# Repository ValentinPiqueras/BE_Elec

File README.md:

# BE_Elec
Valentin PIQUERAS et Solène DUMAS-GROLLIER
(Groupe E)

Nous avons réalisé le routage, et voici donc notre proposition de routage, cf commit "Proposition Routage Final".

Vous trouverez tous les fichiers corrects dans le dossier PropositionRoutage.

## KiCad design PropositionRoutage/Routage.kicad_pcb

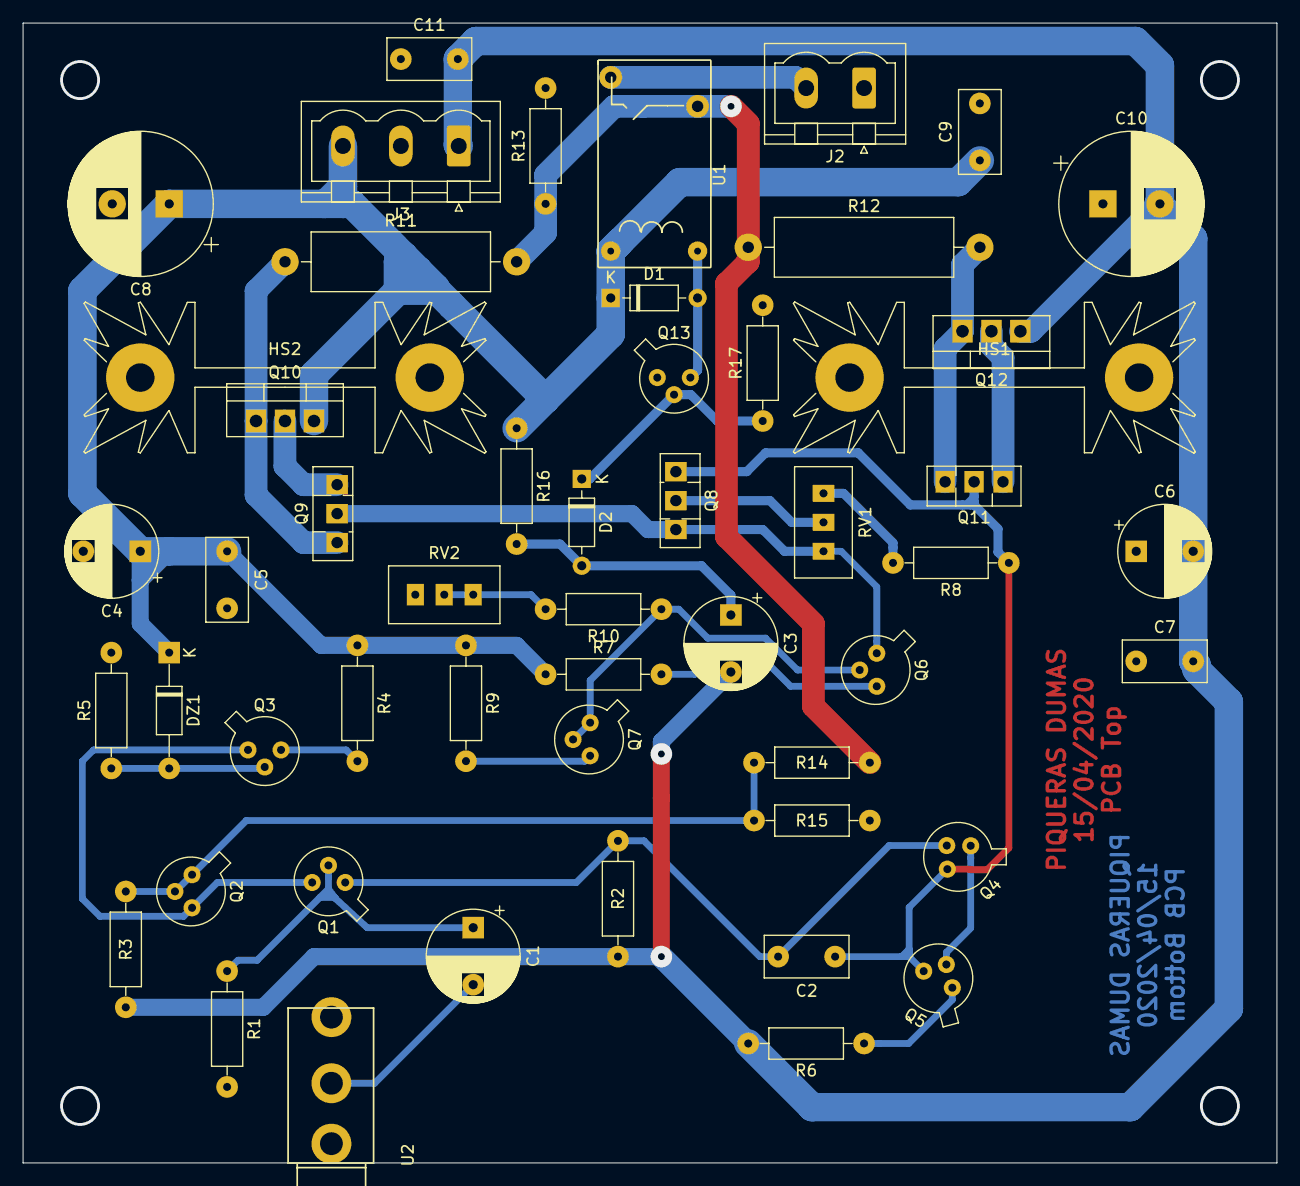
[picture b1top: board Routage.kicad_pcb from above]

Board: 2 copper layers, 110.0 x 100.0 mm, 52 parts (0 on the bottom side), 29 nets.

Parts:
C1, C3: 47u; CP_Radial_D8.0mm_P5.00mm
C2: C; C_Rect_L7.2mm_W3.5mm_P5.00mm_FKS2_FKP2_MKS2_MKP2
C4, C6: 10u; CP_Radial_D8.0mm_P5.00mm
C5, C7, C9, C11: 100n; C_Rect_L7.2mm_W3.5mm_P5.00mm_FKS2_FKP2_MKS2_MKP2
C8, C10: 470u; CP_Radial_D12.5mm_P5.00mm
D1, D2: 1N4148; D_DO-35_SOD27_P7.62mm_Horizontal
DZ1: D_Zener_ALT; D_DO-35_SOD27_P10.16mm_Horizontal
HS1, HS2: Heatsink; Heatsink_Fischer_SK104-STC-STIC_35x13mm_2xDrill2.5mm
J2: Conn_01x02; PhoenixContact_MSTBVA_2,5_2-G-5,08_1x02_P5.08mm_Vertical
J3: Conn_01x03; PhoenixContact_MSTBVA_2,5_3-G-5,08_1x03_P5.08mm_Vertical
Q1, Q2, Q3, Q6, Q7: 2N2907; TO-18-3
Q4, Q5, Q13: 2N2222; TO-18-3
Q8, Q9: BD139; TO-126-3_Vertical
Q10: TIP32; TO-220-3_Vertical
Q11: BD138; TO-126-3_Vertical
Q12: TIP31; TO-220-3_Vertical
R1, R2, R3, R4, R5, R6, R7, R8, R9, R10, R13, R14, R15, R16, R17: R; R_Axial_DIN0207_L6.3mm_D2.5mm_P10.16mm_Horizontal
R11, R12: R; R_Axial_DIN0516_L15.5mm_D5.0mm_P20.32mm_Horizontal
RV1, RV2: R_POT; Potentiometer_Bourns_3296W_Vertical
U1: Relay_1CT; Relais_112LMH2
U2: Jack_Mono; Jack_35RAPC2AV

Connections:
+12V: C4.1, C5.1, C8.1, C9.1, D1.1, DZ1.1, J3.3, Q10.3, R4.1, R7.1, R9.1, R16.1, U1.b2
-12V: C3.2, C6.2, C7.2, C10.2, C11.2, J3.1, Q12.1, R2.2, R3.2, R6.2
/U1-J2: J2.2, U1.c2
/U1-Q13: D1.2, Q13.3, U1.b1
/U1-pp: R11.2, R12.1, R13.1, R14.1, U1.c1
/i(c11||b12): Q11.1, Q12.2
/iC3: C3.1, D2.2, R16.2
/iR11: Q9.1, Q10.1, R11.1
/iR12: Q11.3, Q12.3, R12.2
/iR17: D2.1, Q13.2, R17.1
/ib1: C1.1, Q1.2, R1.1
/ib2: Q2.1, Q2.2, R3.1, R14.2, R15.1
/ic1: C2.2, Q1.1, Q4.2, R2.1
/ie1: Q1.3, Q2.3, Q3.1
/jackcp: C1.2, U2.T
GND: C4.2, C5.2, C6.1, C7.1, C8.2, C9.2, C10.1, C11.1, J2.1, J3.2, Q13.1, R1.2, R5.2, R13.2, R15.2, R17.2, RV2.3, U2.G
unnamed: C2.1, Q4.3, Q5.3, Q8.1, Q11.2, R8.1
unnamed: DZ1.2, Q3.2, R5.1
unnamed: Q3.3, R4.2
unnamed: Q4.1, Q5.2
unnamed: Q5.1, R6.1
unnamed: Q6.1, Q8.3, Q9.2, RV1.1
unnamed: Q6.2, Q7.1, Q7.2, R10.1
unnamed: Q6.3, R7.2
unnamed: Q7.3, R9.2
unnamed: Q8.2, RV1.2
unnamed: Q9.3, Q10.2
unnamed: R8.2, RV1.3
unnamed: R10.2, RV2.1, RV2.2

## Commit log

2020-04-15 Proposition Routage
2020-04-15 Proposition Routage final
2020-05-25 --all
